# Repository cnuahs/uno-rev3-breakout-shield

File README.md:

# uno-rev3-breakout-shield

Compact screw terminal breakout/prototyping shield for Arduino UNO Rev3/4.

# Features

* standard Arduino header signals brought out to compact 3.5mm-pitch screw terminals (e.g., Dinkle [ED350V-XXP](https://www.dinkle.com/en/terminalno/ED350V-XXP)).
* 0.1"-pitch prototyping area, inc. 5V and GND rails.
* standard Arduino UNO Rev3/4 shield footprint (no "wings").

<div style="display:flex;">

</div>

# License
<br />This work is licensed under a [Creative Commons Attribution-ShareAlike 4.0 International License](http://creativecommons.org/licenses/by-sa/4.0/).

# Dependencies
Custom PCB footprints and device definitions can be found [here](https://github.com/cnuahs/custom-eagle-lbr).

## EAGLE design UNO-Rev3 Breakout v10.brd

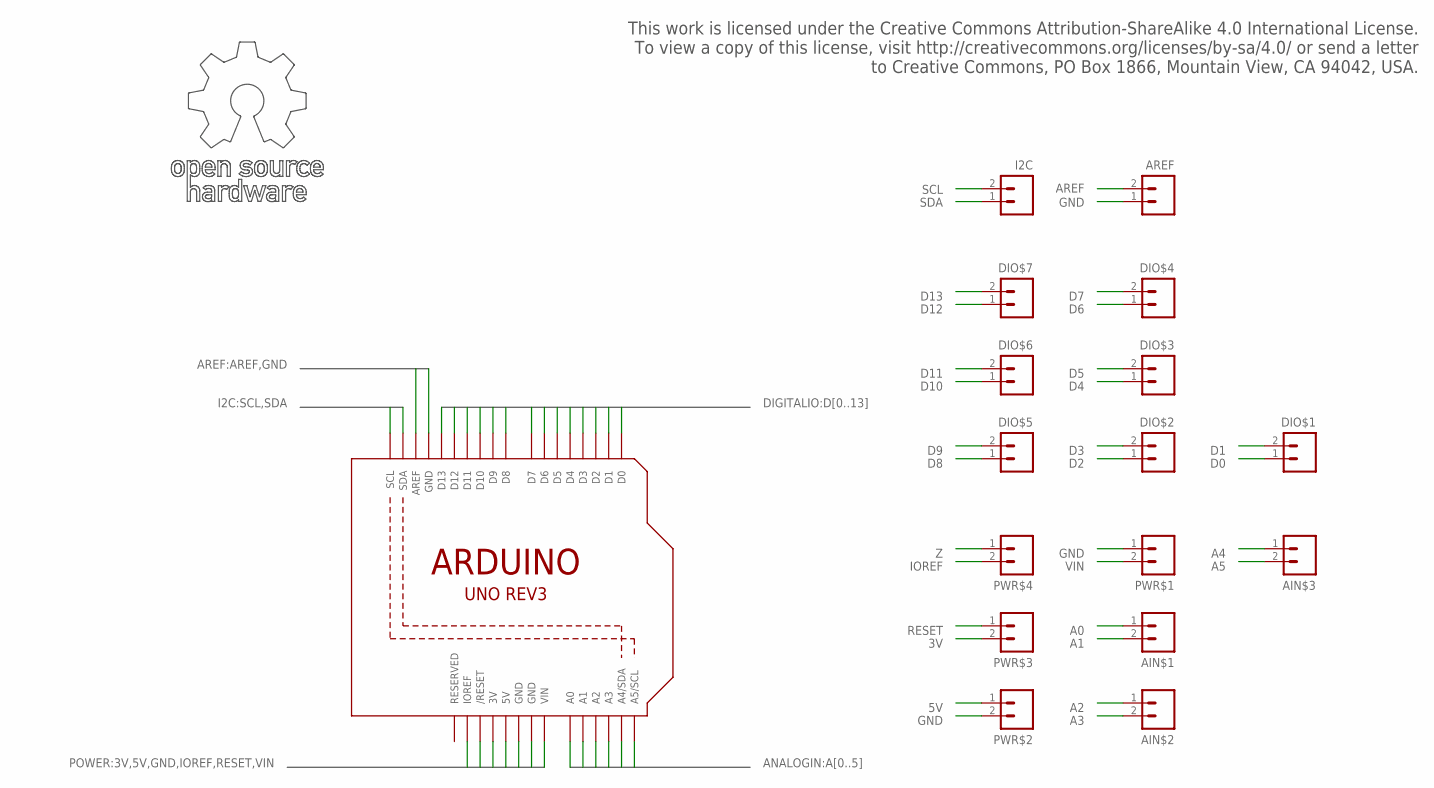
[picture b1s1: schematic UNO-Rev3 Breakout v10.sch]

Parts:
AIN$1, AIN$2, AIN$3: 2-WAY_3.5MM_SCREWTERMINALMINIMAL; DINKEL-1X2-3.5MMSCREW_MINIMAL
AREF: 2-WAY_3.5MM_SCREWTERMINALMINIMAL; DINKEL-1X2-3.5MMSCREW_MINIMAL
DIO$1, DIO$2, DIO$3, DIO$4, DIO$5, DIO$6, DIO$7: 2-WAY_3.5MM_SCREWTERMINALMINIMAL; DINKEL-1X2-3.5MMSCREW_MINIMAL
I2C: 2-WAY_3.5MM_SCREWTERMINALMINIMAL; DINKEL-1X2-3.5MMSCREW_MINIMAL
PWR$1, PWR$2, PWR$3, PWR$4: 2-WAY_3.5MM_SCREWTERMINALMINIMAL; DINKEL-1X2-3.5MMSCREW_MINIMAL
U$1: ARDUINO-UNO-REV3_SHIELD; ARDUINOR3_SHORT_NOLABELS
U$6: OSHW_LOGO; OSHW_10MM

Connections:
3V: PWR$3.2, U$1.3V
5V: PWR$2.1, U$1.5V
A0: AIN$1.1, U$1.A0
A1: AIN$1.2, U$1.A1
A2: AIN$2.1, U$1.A2
A3: AIN$2.2, U$1.A3
A4: AIN$3.1, U$1.A4 (A4/SDA)
A5: AIN$3.2, U$1.A5 (A5/SCL)
AREF: AREF.2, U$1.AREF
D0: DIO$1.1, U$1.D0
D1: DIO$1.2, U$1.D1
D2: DIO$2.1, U$1.D2
D3: DIO$2.2, U$1.D3
D4: DIO$3.1, U$1.D4
D5: DIO$3.2, U$1.D5
D6: DIO$4.1, U$1.D6
D7: DIO$4.2, U$1.D7
D8: DIO$5.1, U$1.D8
D9: DIO$5.2, U$1.D9
D10: DIO$6.1, U$1.D10
D11: DIO$6.2, U$1.D11
D12: DIO$7.1, U$1.D12
D13: DIO$7.2, U$1.D13
GND: AREF.1, PWR$1.1, PWR$2.2, U$1.GND, U$1.GND@1 (GND), U$1.GND@2 (GND)
IOREF: PWR$4.2, U$1.IOREF
RESET: PWR$3.1, U$1.RESET (/RESET)
SCL: I2C.2, U$1.SCL
SDA: I2C.1, U$1.SDA
VIN: PWR$1.2, U$1.VIN
Z: PWR$4.1

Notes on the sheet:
This work is licensed under the Creative Commons Attribution-ShareAlike 4.0 International License. To view a copy of this license, visit http://creativecommons.org/licenses/by-sa/4.0/ or send a letter to Creative Commons, PO Box 1866, Mountain View, CA 94042, USA.

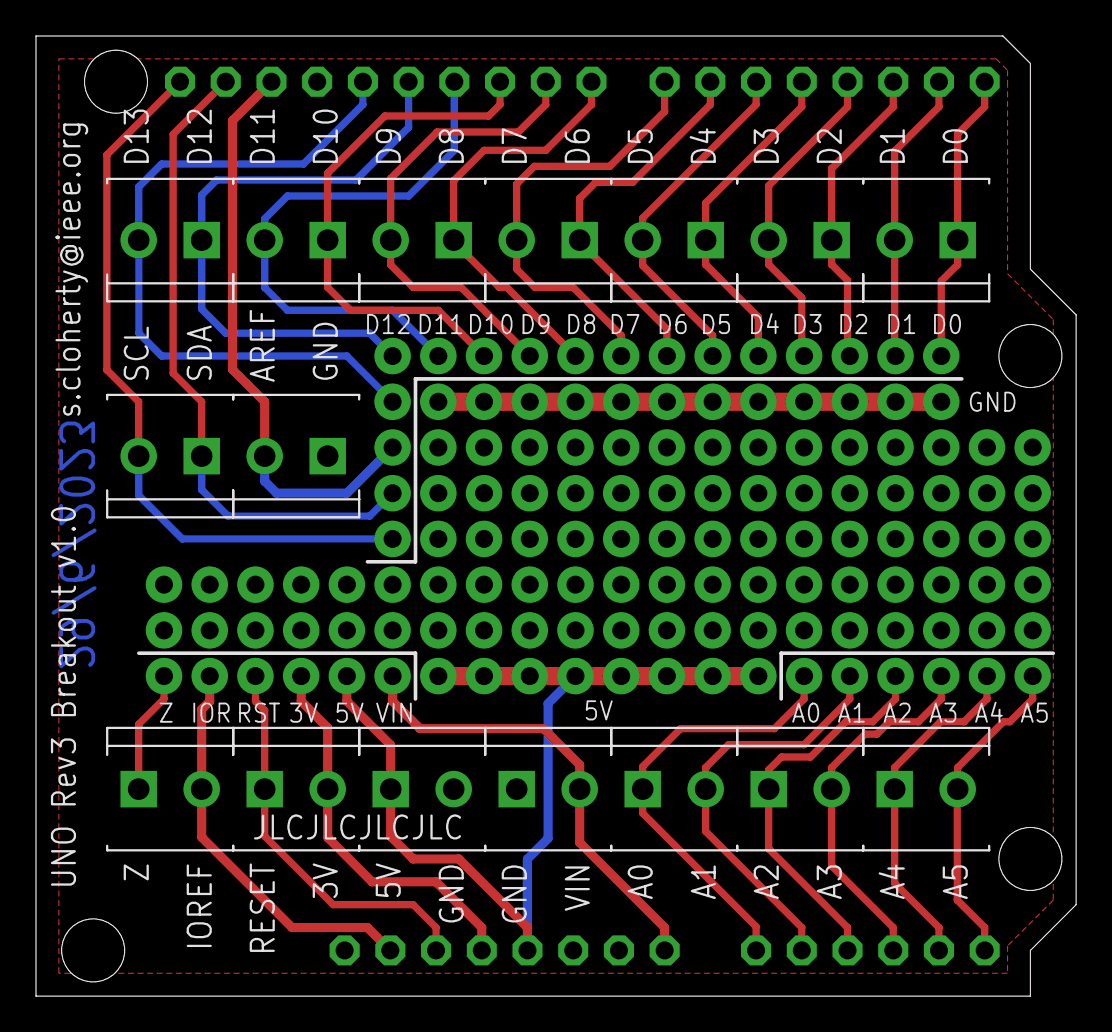
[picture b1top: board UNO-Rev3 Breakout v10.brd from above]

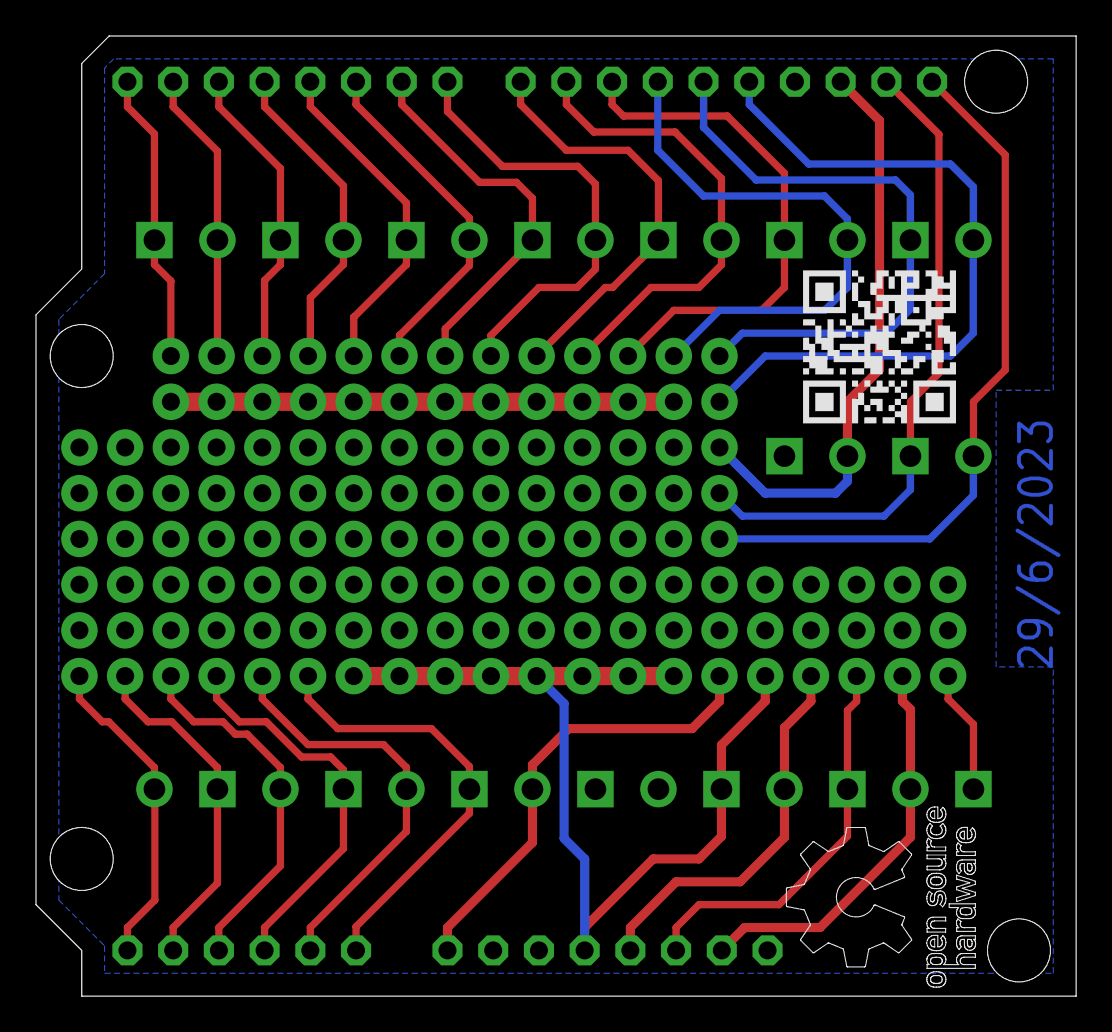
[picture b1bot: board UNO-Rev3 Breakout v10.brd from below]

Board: 2 copper layers, 57.8 x 53.3 mm, 23 parts (2 on the bottom side), 29 nets.

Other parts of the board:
U$2, U$3, U$4, U$5: STAND-OFF
U$8: QRCODE_GITHUB_8.5MM

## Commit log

2023-06-30 Initial commit.
2023-07-01 Update silkscreen overlay.
